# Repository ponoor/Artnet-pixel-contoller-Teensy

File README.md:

# Artnet-pixel-contoller-Teensy
A simple addressable LED controller with Art-Net.

We choose Teensy4.1 to reduce components around Ethernet. It is bit too luxury for this application but still much cheaper than serious commercial pixel controllers.

- Firmware by niimi
- Hardware by kanta

<!--

-->

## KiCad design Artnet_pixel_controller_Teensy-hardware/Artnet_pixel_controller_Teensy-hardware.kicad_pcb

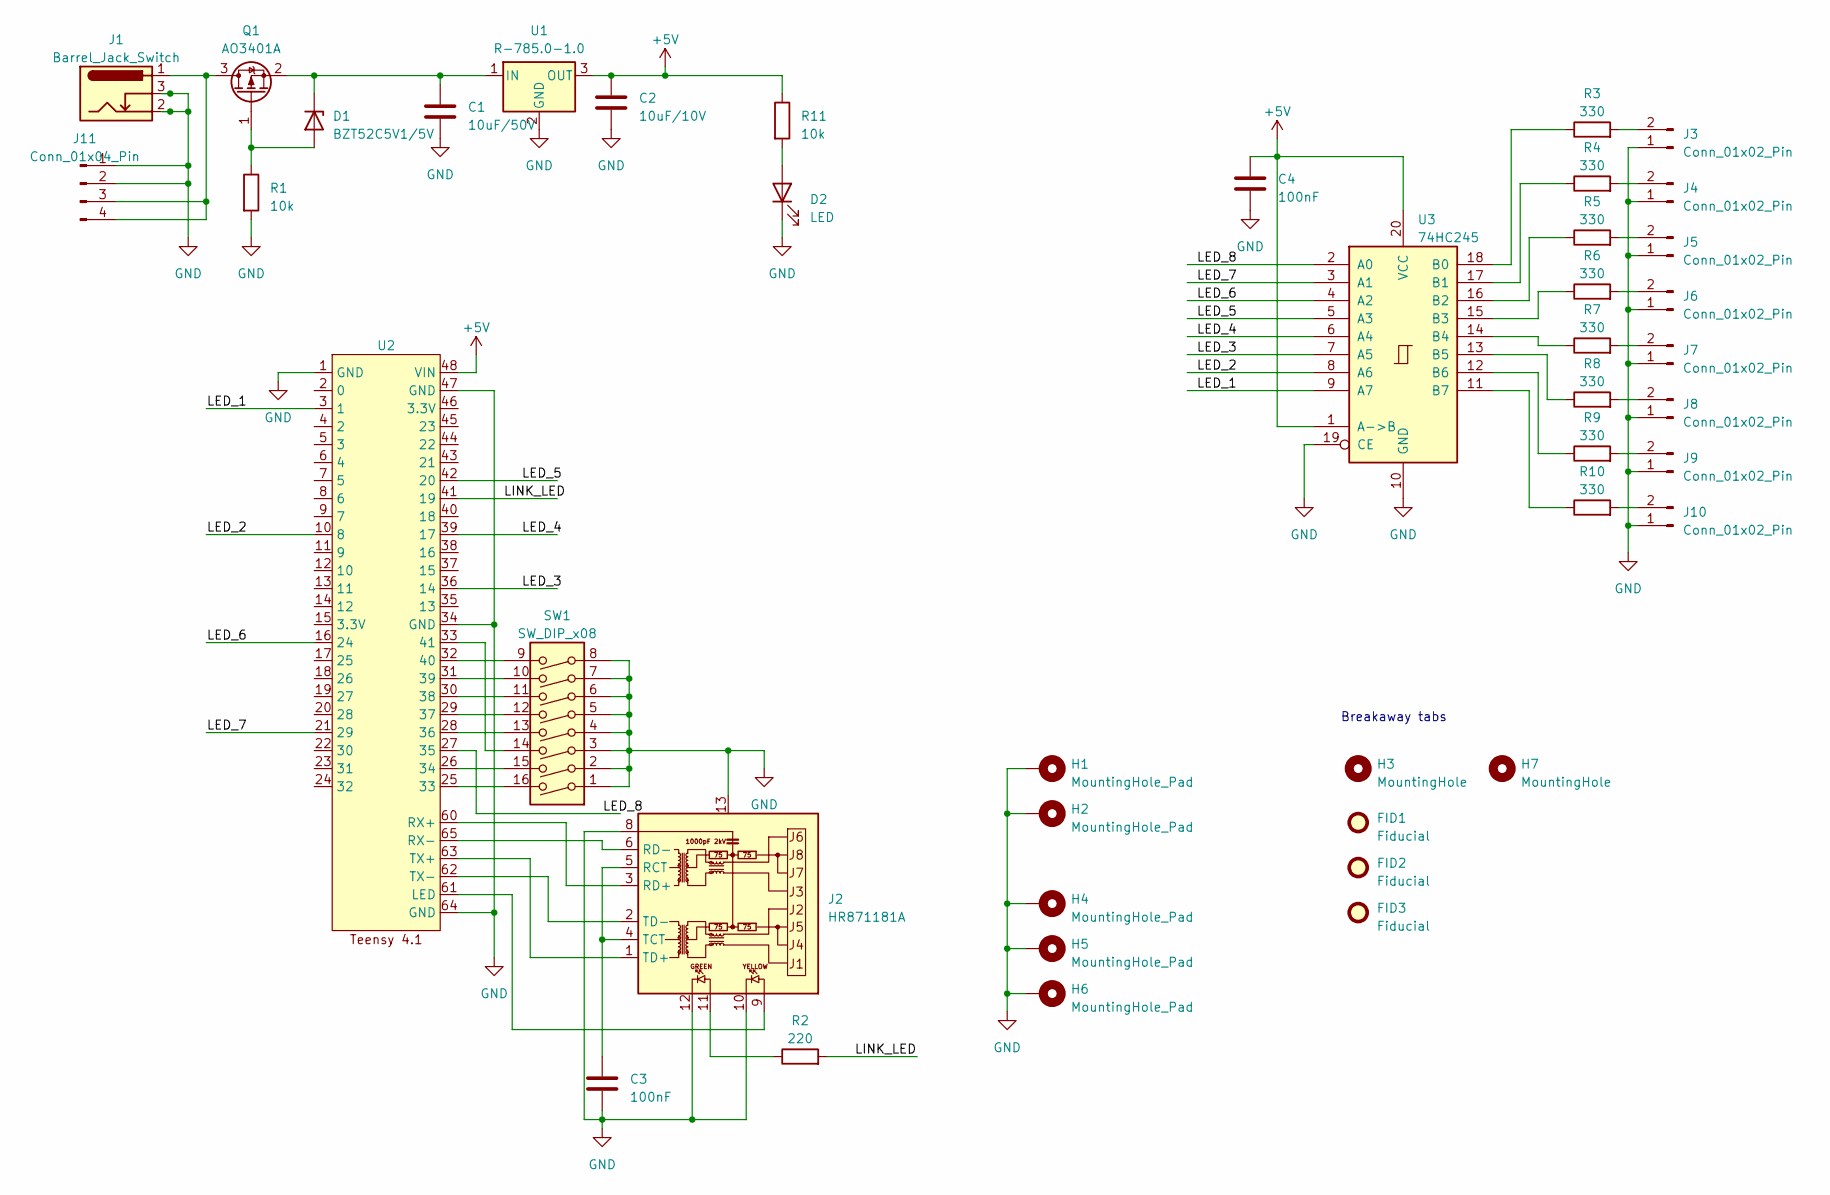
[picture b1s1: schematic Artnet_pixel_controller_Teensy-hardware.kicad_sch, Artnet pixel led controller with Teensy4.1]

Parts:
C1: 10uF/50V; C_1206_3216Metric
C2: 10uF/10V; C_0805_2012Metric
C3, C4: 100nF; C_0603_1608Metric
D1: BZT52C5V1/5V; D_SOD-123F
D2: LED; LED_0603_1608Metric
FID1, FID2, FID3: Fiducial; Fiducial_1mm_Mask3mm
H1, H2, H4, H5, H6: MountingHole_Pad; MountingHole_3.2mm_M3_Pad
H3, H7: MountingHole; MountingHole_4mm
J1: Barrel_Jack_Switch; BarrelJack_GCT_DCJ200-10-A_Horizontal
J2: HR871181A
J3, J4, J5, J6, J7, J8, J9, J10: Conn_01x02_Pin; PhoenixContact_MC_1,5_2-G-3.81_1x02_P3.81mm_Horizontal
J11: Conn_01x04_Pin; PhoenixContact_MC_1,5_4-G-3.81_1x04_P3.81mm_Horizontal
Q1: AO3401A; SOT-23
R1, R11: 10k; R_0603_1608Metric
R2: 220; R_0603_1608Metric
R3, R4, R5, R6, R7, R8, R9, R10: 330; R_0603_1608Metric
SW1: SW_DIP_x08; SW_DIP_SPSTx08_Piano_10.8x21.88mm_W7.62mm_P2.54mm
U1: R-785.0-1.0; Converter_DCDC_RECOM_R-78E-0.5_THT
U2: Teensy41_bothside+ETH
U3: 74HC245; TSSOP-20_4.4x6.5mm_P0.65mm

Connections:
+5V: C2.1, C4.1, R11.1, U1.3 (OUT), U2.48 (VIN), U3.1 (A->B), U3.20 (VCC)
/LED_1: U2.3 (1), U3.9 (A7)
/LED_2: U2.10 (8), U3.8 (A6)
/LED_3: U2.36 (14), U3.7 (A5)
/LED_4: U2.39 (17), U3.6 (A4)
/LED_5: U2.42 (20), U3.5 (A3)
/LED_6: U2.16 (24), U3.4 (A2)
/LED_7: U2.21 (29), U3.3 (A1)
/LED_8: U2.27 (35), U3.2 (A0)
/LINK_LED: R2.2, U2.41 (19)
GND: C1.2, C2.2, C3.2, C4.2, D2.1 (K), H1.1, H2.1, H4.1, H5.1, H6.1, J1.2, J1.3, J2.8, J2.10, J2.12, J2.13, J3.1, J4.1, J5.1, J6.1, J7.1, J8.1, J9.1, J10.1, J11.1, J11.2, R1.2, SW1.1, SW1.2, SW1.3, SW1.4, SW1.5, SW1.6, SW1.7, SW1.8, U1.2 (GND), U2.1 (GND), U2.34 (GND), U2.47 (GND), U2.64 (GND), U3.10 (GND), U3.19 (CE); also elsewhere on the board
unnamed: D1.2 (A), Q1.1 (G), R1.1
unnamed: C1.1, D1.1 (K), Q1.2 (S), U1.1 (IN)
unnamed: D2.2 (A), R11.2
unnamed: J2.11, R2.1
unnamed: C3.1, J2.4 (TCT), J2.5 (RCT)
unnamed: J2.3 (RD+), U2.60 (RX+)
unnamed: J2.6 (RD-), U2.65 (RX-)
unnamed: J2.1 (TD+), U2.63 (TX+)
unnamed: J2.2 (TD-), U2.62 (TX-)
unnamed: J3.2, R3.2
unnamed: J4.2, R4.2
unnamed: J5.2, R5.2
unnamed: J6.2, R6.2
unnamed: J7.2, R7.2
unnamed: J8.2, R8.2
unnamed: J9.2, R9.2
unnamed: J10.2, R10.2
unnamed: J1.1, J11.3, J11.4, Q1.3 (D)
unnamed: SW1.16, U2.25 (33)
unnamed: SW1.15, U2.26 (34)
unnamed: SW1.13, U2.28 (36)
unnamed: SW1.12, U2.29 (37)
unnamed: SW1.11, U2.30 (38)
unnamed: SW1.10, U2.31 (39)
unnamed: SW1.9, U2.32 (40)
unnamed: SW1.14, U2.33 (41)
unnamed: J2.9, U2.61 (LED)
unnamed: R3.1, U3.18 (B0)
unnamed: R4.1, U3.17 (B1)
unnamed: R5.1, U3.16 (B2)
unnamed: R6.1, U3.15 (B3)
unnamed: R7.1, U3.14 (B4)
unnamed: R8.1, U3.13 (B5)
unnamed: R9.1, U3.12 (B6)
unnamed: R10.1, U3.11 (B7)

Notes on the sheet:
Breakaway tabs

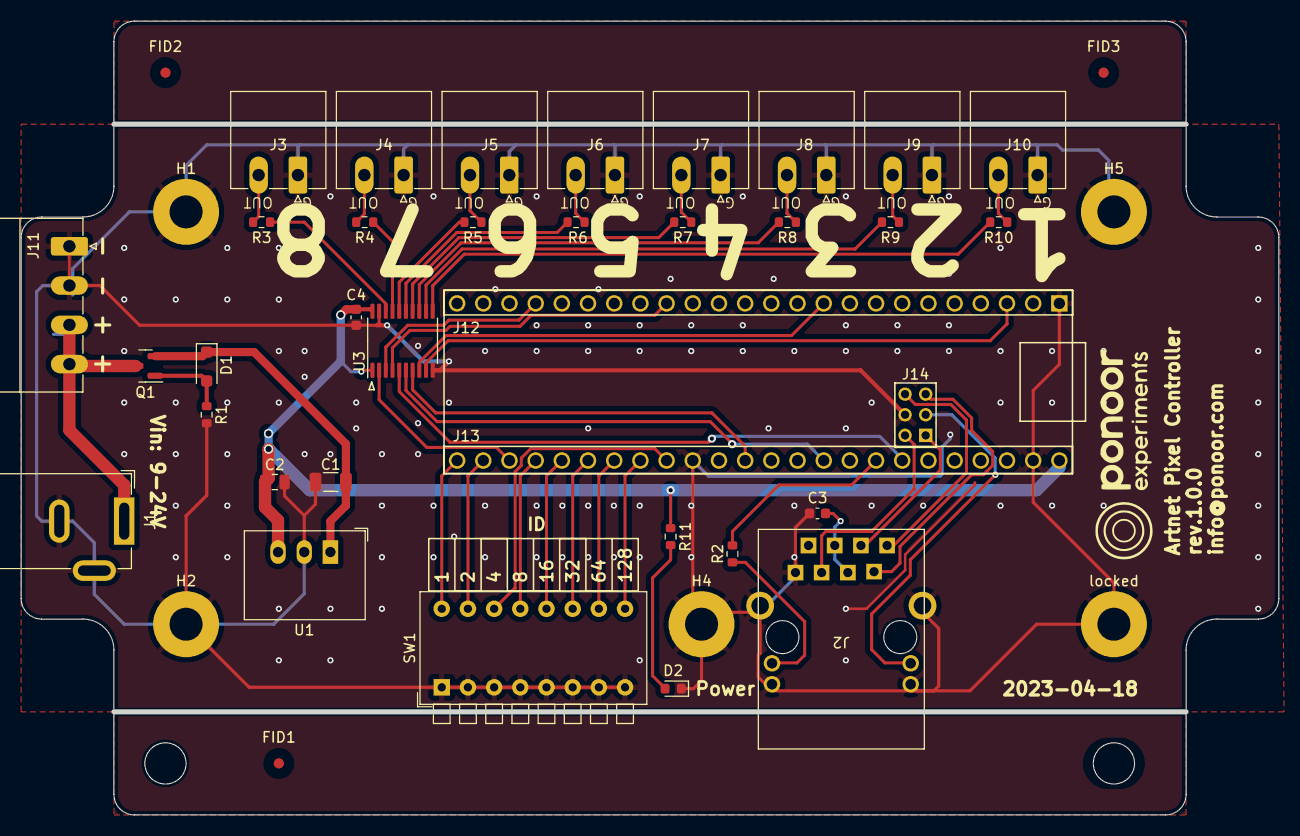
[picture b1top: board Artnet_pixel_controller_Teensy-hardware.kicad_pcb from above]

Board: 2 copper layers, 122.0 x 77.0 mm, 43 parts (0 on the bottom side), 46 nets.

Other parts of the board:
locked: MountingHole_Pad; MountingHole_3.2mm_M3_Pad

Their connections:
GND: locked.1; also elsewhere on the board

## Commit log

2023-04-03 Added KiCad project (still empty)
2023-04-04 回路図と基板上の部品配置を大雑把に置いた
2023-04-05 WS2812Serial用のピン配置に変更
2023-04-06 プロト基板入稿データ
2023-04-12 動作テスト用に使ったコードを追加
2023-04-13 gerber data v1.0.0
2023-04-17 LED出力の番号を入れ替え
2023-04-30 PCB fabrication data
2023-05-08 コミットメント
2023-05-09 oscコマンドを追加して確認した
2023-05-14 Remove .zip production files
2023-05-16 sync来なかったら光る
2023-05-16 link led
2023-05-16 oscで設定をもとに戻す
2023-05-17 ws2812Serialにした
2023-05-18 ファイルの名前を変えた busy実装
2023-05-18 bug fix
2023-05-22 variables
2023-09-02 organize files
2023-09-02 include .csv files to the repo
